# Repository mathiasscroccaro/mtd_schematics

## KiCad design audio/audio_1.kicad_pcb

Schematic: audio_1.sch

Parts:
D1: LED; LED_D3.0mm
J1: Conn_01x06; Molex_KK-6410-06_06x2.54mm_Straight
J2: Esquerdo; Pin_Header_Angled_1x06_Pitch2.54mm
J3: Direito; Pin_Header_Angled_1x06_Pitch2.54mm
Q1: BC548; TO-92_Inline_Narrow_Oval
R1: 100; R_1206_HandSoldering
R2: 2700; R_1206_HandSoldering

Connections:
3.3v: J1.6, J2.6, J3.1, J3.6, R1.2
unnamed: D1.1, Q1.1 (C)
unnamed: D1.2, R1.1
unnamed: J1.1, R2.2
unnamed: Q1.2 (B), R2.1
bclk: J1.4, J2.4, J3.4
dout: J1.3, J2.3, J3.3
gnd: J1.5, J2.1, J2.5, J3.5, Q1.3 (E)
lrcl: J1.2, J2.2, J3.2

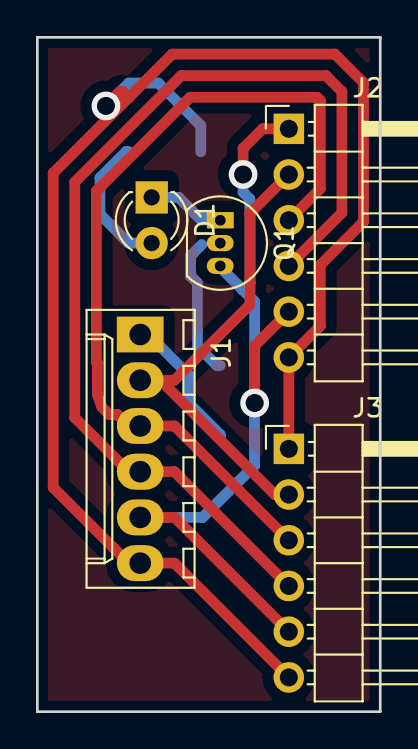
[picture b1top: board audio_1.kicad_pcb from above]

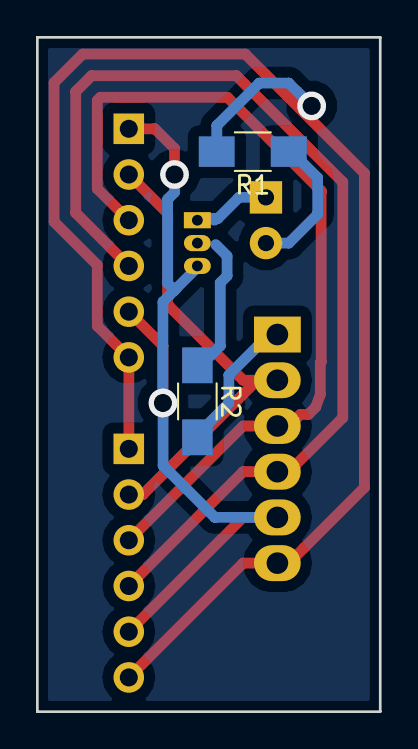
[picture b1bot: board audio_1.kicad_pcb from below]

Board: 2 copper layers, 19.1 x 37.5 mm, 7 parts (2 on the bottom side), 9 nets.

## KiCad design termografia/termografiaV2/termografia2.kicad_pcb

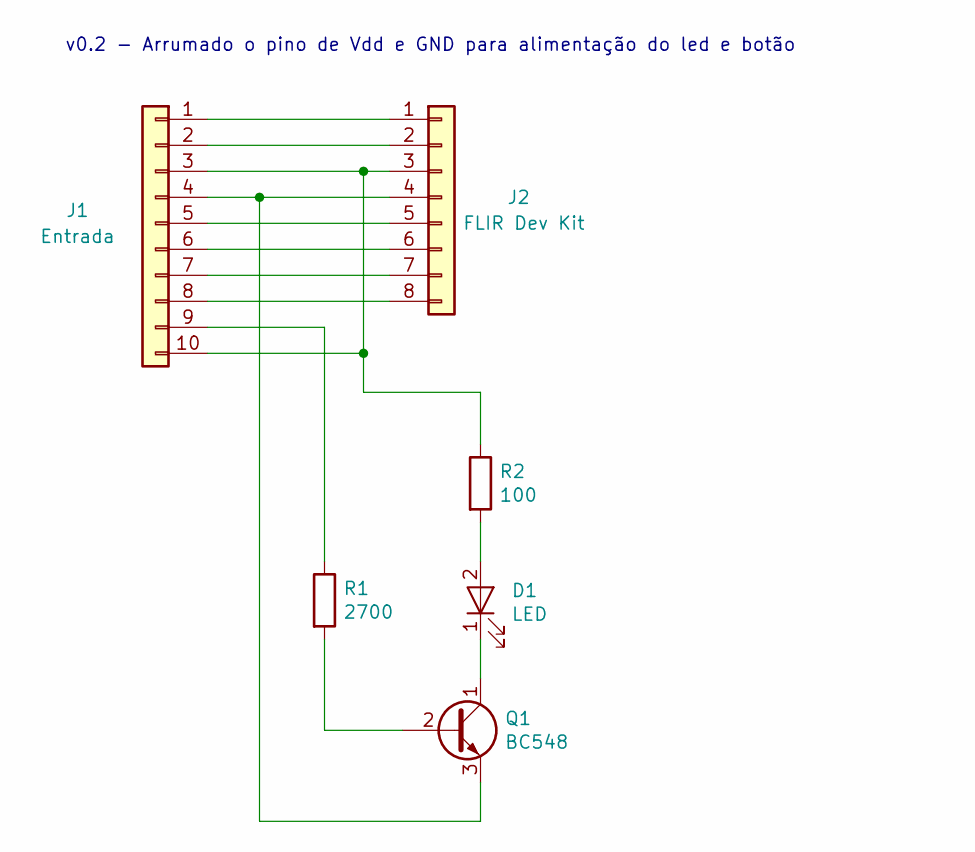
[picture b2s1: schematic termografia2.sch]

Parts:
D1: LED; LED_D3.0mm
J1: Entrada; Pin_Header_Straight_1x10_Pitch2.54mm
J2: FLIR Dev Kit; Pin_Header_Straight_1x08_Pitch2.54mm
Q1: BC548; TO-92_Inline_Wide
R1: 2700; R_Axial_DIN0207_L6.3mm_D2.5mm_P10.16mm_Horizontal
R2: 100; R_Axial_DIN0207_L6.3mm_D2.5mm_P10.16mm_Horizontal

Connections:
unnamed: D1.1 (K), Q1.1 (C)
unnamed: D1.2 (A), R2.2
unnamed: J1.1, J2.1
unnamed: J1.2, J2.2
unnamed: J1.4, J2.4, Q1.3 (E)
unnamed: J1.5, J2.5
unnamed: J1.6, J2.6
unnamed: J1.7, J2.7
unnamed: J1.8, J2.8
unnamed: J1.9, R1.1
unnamed: J1.3, J1.10, J2.3, R2.1
unnamed: Q1.2 (B), R1.2

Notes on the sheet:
v0.2 - Arrumado o pino de Vdd e GND para alimentação do led e botão

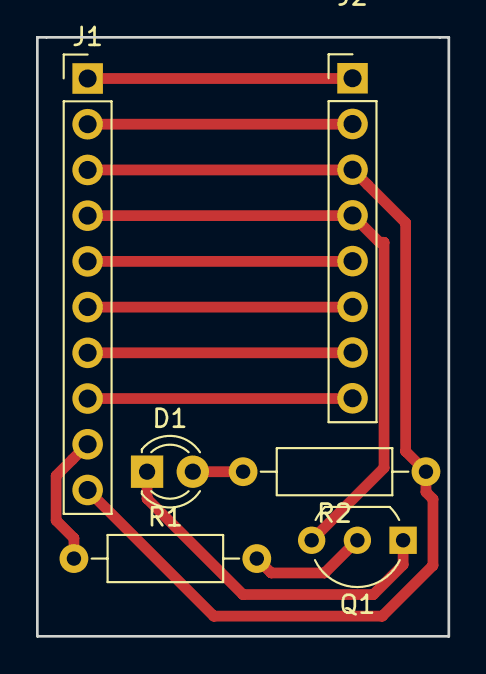
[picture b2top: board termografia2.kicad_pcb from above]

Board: 2 copper layers, 22.9 x 33.3 mm, 6 parts (0 on the bottom side), 12 nets.

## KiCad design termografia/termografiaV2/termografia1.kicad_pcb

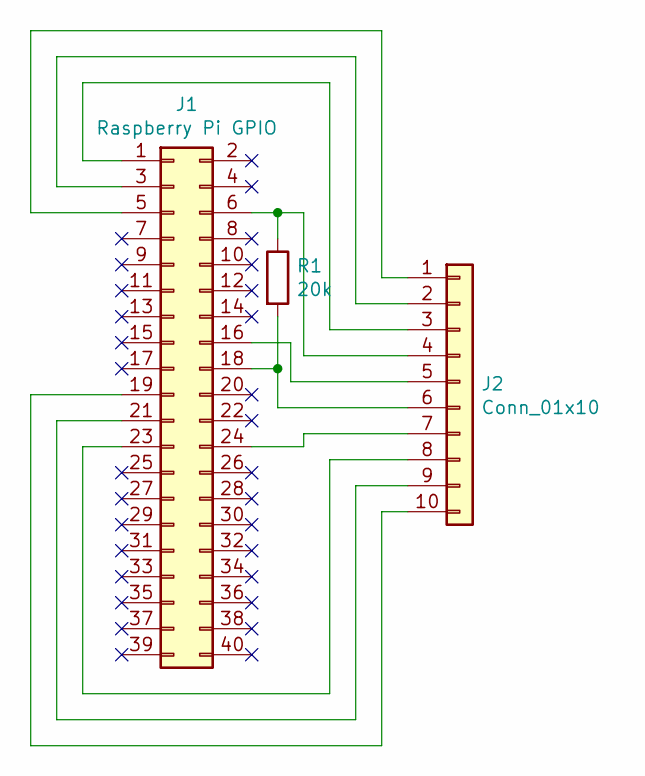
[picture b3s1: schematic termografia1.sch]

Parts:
J1: Raspberry Pi GPIO; Pin_Header_Straight_2x20_Pitch2.54mm
J2: Conn_01x10; Pin_Header_Straight_1x10_Pitch2.54mm
R1: 20k; R_Axial_DIN0411_L9.9mm_D3.6mm_P15.24mm_Horizontal

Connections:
unnamed: J1.1, J2.3
unnamed: J1.3, J2.2
unnamed: J1.5, J2.1
unnamed: J1.6, J2.4, R1.1
unnamed: J1.16, J2.5
unnamed: J1.18, J2.6, R1.2
unnamed: J1.19, J2.10
unnamed: J1.21, J2.9
unnamed: J1.23, J2.8
unnamed: J1.24, J2.7

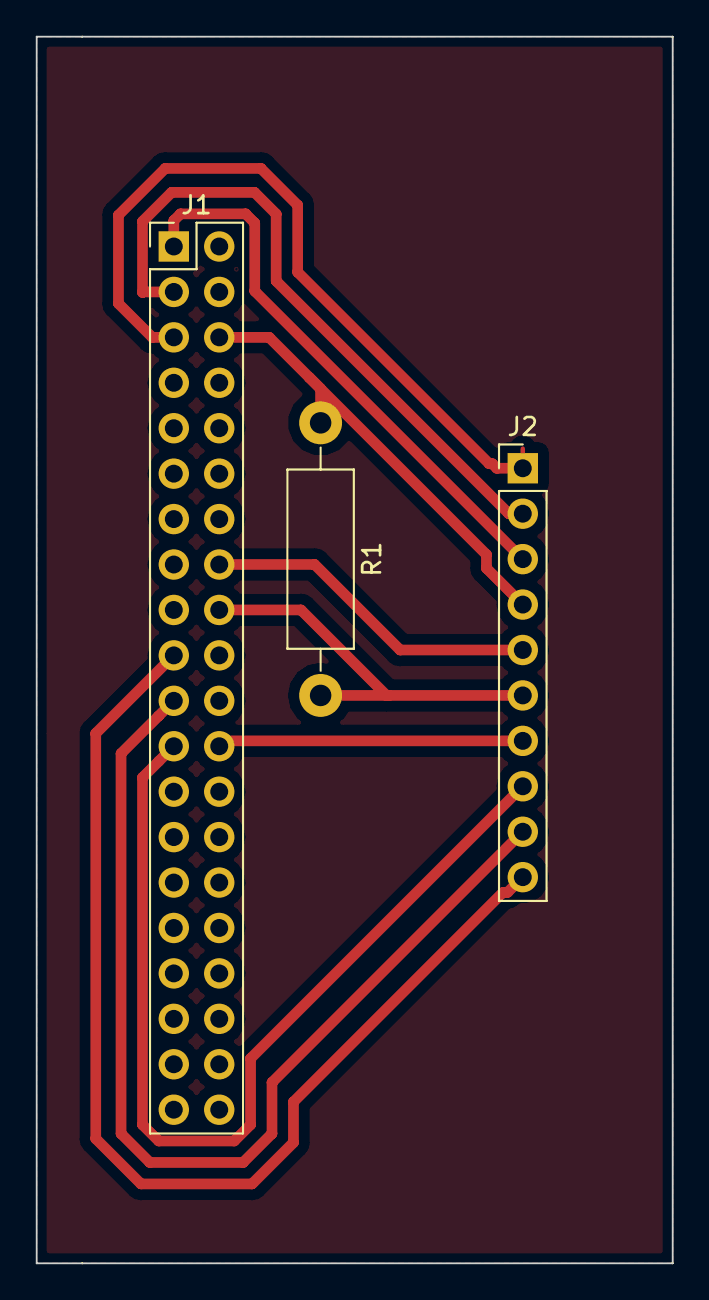
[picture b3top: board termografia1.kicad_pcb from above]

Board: 2 copper layers, 35.6 x 68.6 mm, 3 parts (0 on the bottom side), 10 nets.

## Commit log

2018-05-02 Captação de audio OK
2018-05-04 Falta implementar o layout da placa de áudio, esquemático pronto
2018-10-12 Corrigida alimentação do led, botão e resistor de pull down
